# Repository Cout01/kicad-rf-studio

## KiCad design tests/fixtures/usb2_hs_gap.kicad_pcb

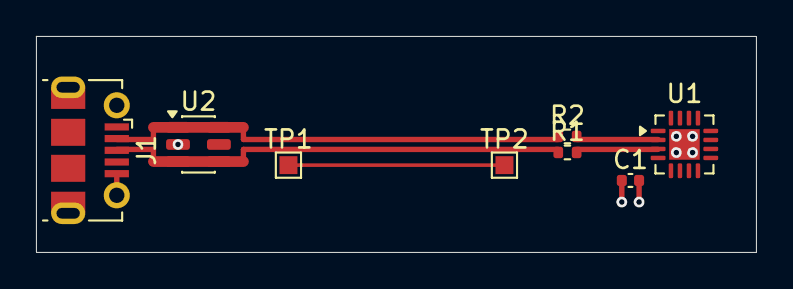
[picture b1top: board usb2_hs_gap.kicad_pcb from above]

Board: 4 copper layers, 40.0 x 12.0 mm, 8 parts (0 on the bottom side), 7 nets.

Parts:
C1: 100nF; C_0402_1005Metric
J1: USB_B_Micro; USB_Micro-B_Molex-105017-0001
R1, R2: 22; R_0402_1005Metric
TP1, TP2: TP; TestPoint_Pad_1.0x1.0mm
U1: MCU; QFN-16-1EP_3x3mm_P0.5mm_EP1.7x1.7mm
U2: USBLC6-2SC6; SOT-23-6

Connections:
AUX: TP1.1, TP2.1
GND: C1.2, J1.5, J1.6, U1.17, U2.2
MCU_D+: R1.2, U1.3
MCU_D-: R2.2, U1.2
USB_D+: J1.3, R1.1, U2.3, U2.4
USB_D-: J1.2, R2.1, U2.1, U2.6
VBUS: J1.1, U2.5
